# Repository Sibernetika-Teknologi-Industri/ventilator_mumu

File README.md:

# venti
Low Cost Ventilator - ITB

## Phase 1:
- Kode stepper awal + Kalibrasi
- Kode nextion awal

## Phase 2:
- Kode Integrasi
- Sampai test awal @ salman (8 April 2020)

## Phase 3:
- Pengembangan SIMV

## Phase 4:
- Pengembangan SIMV Lanjutan

## Phase 6:
- Backup setelah uji pre-klinis
- Persiapan pengembangan lanjutan per 25 Mei 2021

## Phase 8:
- IR Calculation from sensor
- Fighting and Spurious Alarm
- Mandatory Pressure Control

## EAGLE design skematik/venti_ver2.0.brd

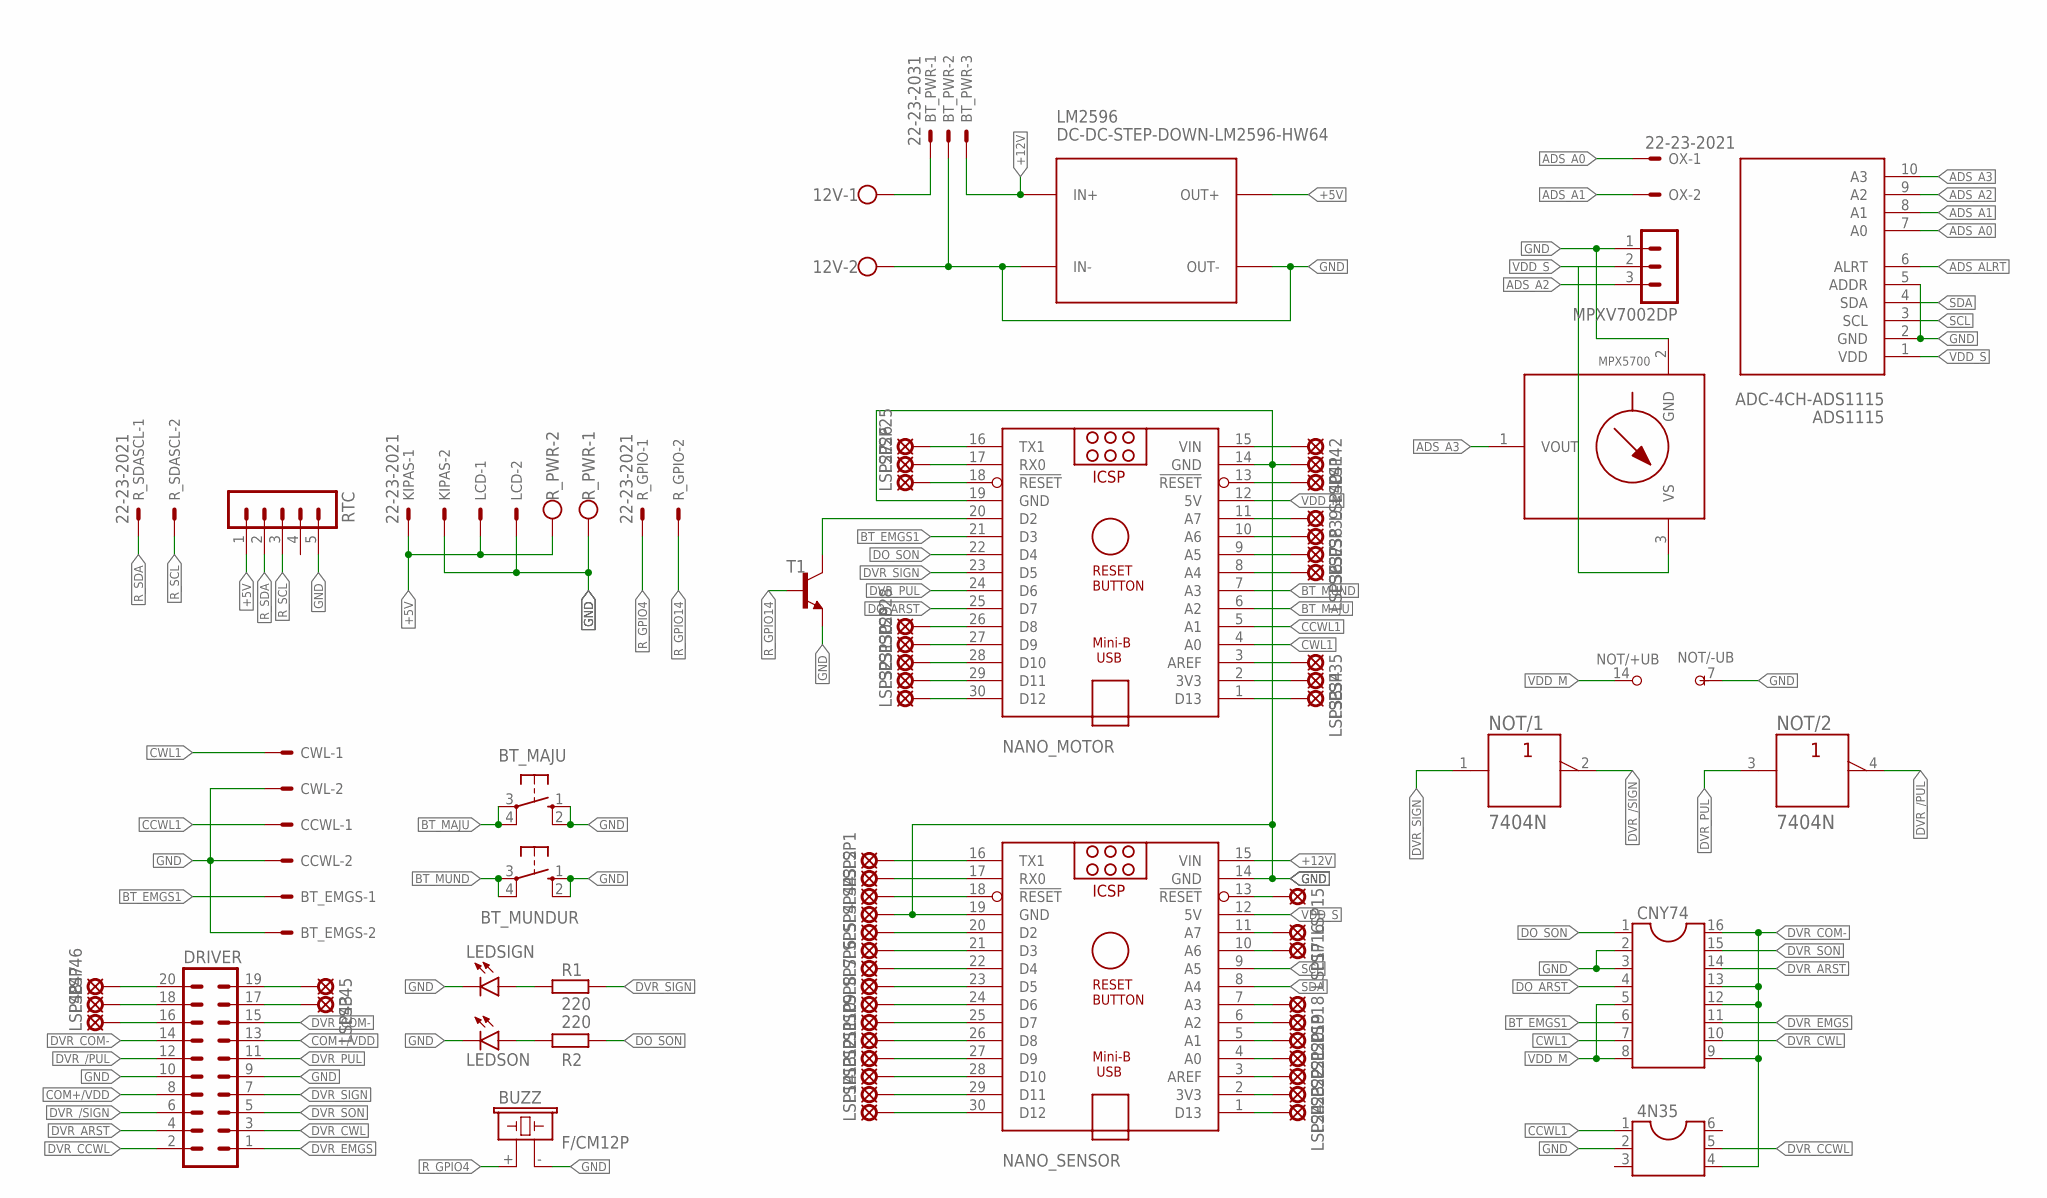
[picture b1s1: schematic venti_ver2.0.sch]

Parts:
4N35: DIL6; DIL06
12V: W237-102
ADS1115: ADC-4CH-ADS1115
BT_EMGS: 22-23-2021
BT_MAJU: 40-XX; B3F-40XX
BT_MUNDUR: 40-XX; B3F-40XX
BT_PWR: 22-23-2031
BUZZ: F/CM12P
CCWL: 22-23-2021
CNY74: DIL16
CWL: 22-23-2021
DRIVER: ML20
KIPAS: 22-23-2021
LCD: 22-23-2021
LEDSIGN: LED5MM
LEDSON: LED5MM
LM2596: DC-DC-STEP-DOWN-LM2596-HW64; DC-DC-STEP-DOWN-LM2596
LSP1, LSP2, LSP3, LSP4, LSP5, LSP6, LSP7, LSP8, LSP9, LSP10, LSP11, LSP12, LSP13, LSP14, LSP15, LSP16, LSP17, LSP18, LSP19, LSP20, LSP21, LSP22, LSP23, LSP24, LSP25, LSP26, LSP27, LSP28, LSP29, LSP30, LSP31, LSP32, LSP33, LSP34, LSP35, LSP36, LSP37, LSP38, LSP39, LSP40, LSP41, LSP42, LSP43, LSP44, LSP45, LSP46, LSP47, LSP48: LSP11
MPX5700: MPX-867B-H; 867B-H
MPXV7002DP: MA03-1
NANO_MOTOR: ARDUINO_NANO
NANO_SENSOR: ARDUINO_NANO
NOT: 7404N; DIL14
OX: 22-23-2021
R1, R2: 220; 0204/7
RTC: MA05-1
R_GPIO: 22-23-2021
R_PWR: W237-102
R_SDASCL: 22-23-2021
T1: 2N2222-NPN-TO92-EBC; TO92-EBC

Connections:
+5V: KIPAS.1, LCD.1, LM2596.OUT+, RTC.1, R_PWR.2
+12V: BT_PWR.3, LM2596.IN+, NANO_SENSOR.15 (VIN)
ADS_A0: ADS1115.7 (A0), OX.1
ADS_A1: ADS1115.8 (A1), OX.2
ADS_A2: ADS1115.9 (A2), MPXV7002DP.3
ADS_A3: ADS1115.10 (A3), MPX5700.1 (VOUT)
ADS_ALRT: ADS1115.6 (ALRT)
BT_EMGS1: BT_EMGS.1, CNY74.6, NANO_MOTOR.21 (D3)
BT_MAJU: BT_MAJU.3, BT_MAJU.4 (P1), NANO_MOTOR.6 (A2)
BT_MUND: BT_MUNDUR.3, BT_MUNDUR.4 (P1), NANO_MOTOR.7 (A3)
CCWL1: 4N35.1, CCWL.1, NANO_MOTOR.5 (A1)
COM+/VDD: DRIVER.8, DRIVER.13
CWL1: CNY74.7, CWL.1, NANO_MOTOR.4 (A0)
DO_ARST: CNY74.4, NANO_MOTOR.25 (D7)
DO_SON: CNY74.1, NANO_MOTOR.22 (D4), R2.2
DVR_/PUL: DRIVER.12, NOT.4 (Y)
DVR_/SIGN: DRIVER.6, NOT.2 (Y)
DVR_ARST: CNY74.14, DRIVER.4
DVR_CCWL: 4N35.5, DRIVER.2
DVR_COM-: 4N35.4, CNY74.9, CNY74.12, CNY74.13, CNY74.16, DRIVER.14, DRIVER.15
DVR_CWL: CNY74.10, DRIVER.3
DVR_EMGS: CNY74.11, DRIVER.1
DVR_PUL: DRIVER.11, NANO_MOTOR.24 (D6), NOT.3 (A)
DVR_SIGN: DRIVER.7, NANO_MOTOR.23 (D5), NOT.1 (A), R1.2
DVR_SON: CNY74.15, DRIVER.5
GND: 4N35.2, 12V.2, ADS1115.2 (GND), ADS1115.5 (ADDR), BT_EMGS.2, BT_MAJU.1 (S), BT_MAJU.2 (S1), BT_MUNDUR.1 (S), BT_MUNDUR.2 (S1), BT_PWR.2, BUZZ.- (2), CCWL.2, CNY74.2, CNY74.3, CWL.2, DRIVER.9, DRIVER.10, KIPAS.2, LCD.2, LEDSIGN.K (C), LEDSON.K (C), LM2596.IN-, LM2596.OUT-, LSP41.MP, LSP44.MP, MPX5700.2 (GND), MPXV7002DP.1, NANO_MOTOR.14 (GND), NANO_MOTOR.19 (GND), NANO_SENSOR.14 (GND), NANO_SENSOR.19 (GND), NOT.7 (-UB), RTC.5, R_PWR.1, T1.E
unnamed: NANO_MOTOR.20 (D2), T1.C
unnamed: LEDSIGN.A, R1.1
unnamed: LEDSON.A, R2.1
unnamed: 12V.1, BT_PWR.1
unnamed: LSP1.MP, NANO_SENSOR.16 (TX1)
unnamed: LSP2.MP, NANO_SENSOR.17 (RX0)
unnamed: LSP3.MP, NANO_SENSOR.18 (!RESET)
unnamed: LSP4.MP, NANO_SENSOR.20 (D2)
unnamed: LSP5.MP, NANO_SENSOR.21 (D3)
unnamed: LSP6.MP, NANO_SENSOR.22 (D4)
unnamed: LSP7.MP, NANO_SENSOR.23 (D5)
unnamed: LSP8.MP, NANO_SENSOR.24 (D6)
unnamed: LSP9.MP, NANO_SENSOR.25 (D7)
unnamed: LSP10.MP, NANO_SENSOR.26 (D8)
unnamed: LSP11.MP, NANO_SENSOR.27 (D9)
unnamed: LSP12.MP, NANO_SENSOR.28 (D10)
unnamed: LSP13.MP, NANO_SENSOR.29 (D11)
unnamed: LSP14.MP, NANO_SENSOR.30 (D12)
unnamed: LSP15.MP, NANO_SENSOR.13 (!RESET)
unnamed: LSP16.MP, NANO_SENSOR.11 (A7)
unnamed: LSP17.MP, NANO_SENSOR.10 (A6)
unnamed: LSP18.MP, NANO_SENSOR.7 (A3)
unnamed: LSP19.MP, NANO_SENSOR.6 (A2)
unnamed: LSP20.MP, NANO_SENSOR.5 (A1)
unnamed: LSP21.MP, NANO_SENSOR.4 (A0)
unnamed: LSP22.MP, NANO_SENSOR.3 (AREF)
unnamed: LSP23.MP, NANO_SENSOR.2 (3V3)
unnamed: LSP24.MP, NANO_SENSOR.1 (D13)
unnamed: LSP25.MP, NANO_MOTOR.16 (TX1)
unnamed: LSP26.MP, NANO_MOTOR.17 (RX0)
unnamed: LSP27.MP, NANO_MOTOR.18 (!RESET)
unnamed: LSP28.MP, NANO_MOTOR.26 (D8)
unnamed: LSP29.MP, NANO_MOTOR.27 (D9)
unnamed: LSP30.MP, NANO_MOTOR.28 (D10)
unnamed: LSP31.MP, NANO_MOTOR.29 (D11)
unnamed: LSP32.MP, NANO_MOTOR.30 (D12)
unnamed: LSP33.MP, NANO_MOTOR.1 (D13)
unnamed: LSP34.MP, NANO_MOTOR.2 (3V3)
unnamed: LSP35.MP, NANO_MOTOR.3 (AREF)
unnamed: LSP36.MP, NANO_MOTOR.8 (A4)
unnamed: LSP37.MP, NANO_MOTOR.9 (A5)
unnamed: LSP38.MP, NANO_MOTOR.10 (A6)
unnamed: LSP39.MP, NANO_MOTOR.11 (A7)
unnamed: LSP40.MP, NANO_MOTOR.13 (!RESET)
unnamed: LSP42.MP, NANO_MOTOR.15 (VIN)
unnamed: DRIVER.17, LSP43.MP
unnamed: DRIVER.19, LSP45.MP
unnamed: DRIVER.16, LSP48.MP
unnamed: DRIVER.18, LSP47.MP
unnamed: DRIVER.20, LSP46.MP
R_GPIO4: BUZZ.+ (1), R_GPIO.1
R_GPIO14: R_GPIO.2, T1.B
R_SCL: RTC.3, R_SDASCL.2
R_SDA: RTC.2, R_SDASCL.1
SCL: ADS1115.3 (SCL), NANO_SENSOR.9 (A5)
SDA: ADS1115.4 (SDA), NANO_SENSOR.8 (A4)
VDD_M: CNY74.5, CNY74.8, NANO_MOTOR.12 (5V), NOT.14 (+UB)
VDD_S: ADS1115.1 (VDD), MPX5700.3 (VS), MPXV7002DP.2, NANO_SENSOR.12 (5V)

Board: 2 copper layers, 78 parts (3 on the bottom side), 83 nets, no tracks yet.

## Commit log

2021-05-27 Added Dokumentasi Kalibrasi dan Pra Klinis
2021-05-27 Update Annotation
2021-06-04 Added latest schematics
2021-06-07 Update dokumen
2021-06-07 Update dokumen planning
2021-06-08 Update structured skematik
2021-06-28 commit 28 June to development 2021
2021-08-05 update 4/8/21
2021-09-09 Create LICENSE
2021-09-30 Mandatory Pressure Control

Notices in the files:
parts and their libraries:
diy-modules: Released under the Creative Commons Attribution 4.0 International License: http://creativecommons.org/licenses/by/4.0
